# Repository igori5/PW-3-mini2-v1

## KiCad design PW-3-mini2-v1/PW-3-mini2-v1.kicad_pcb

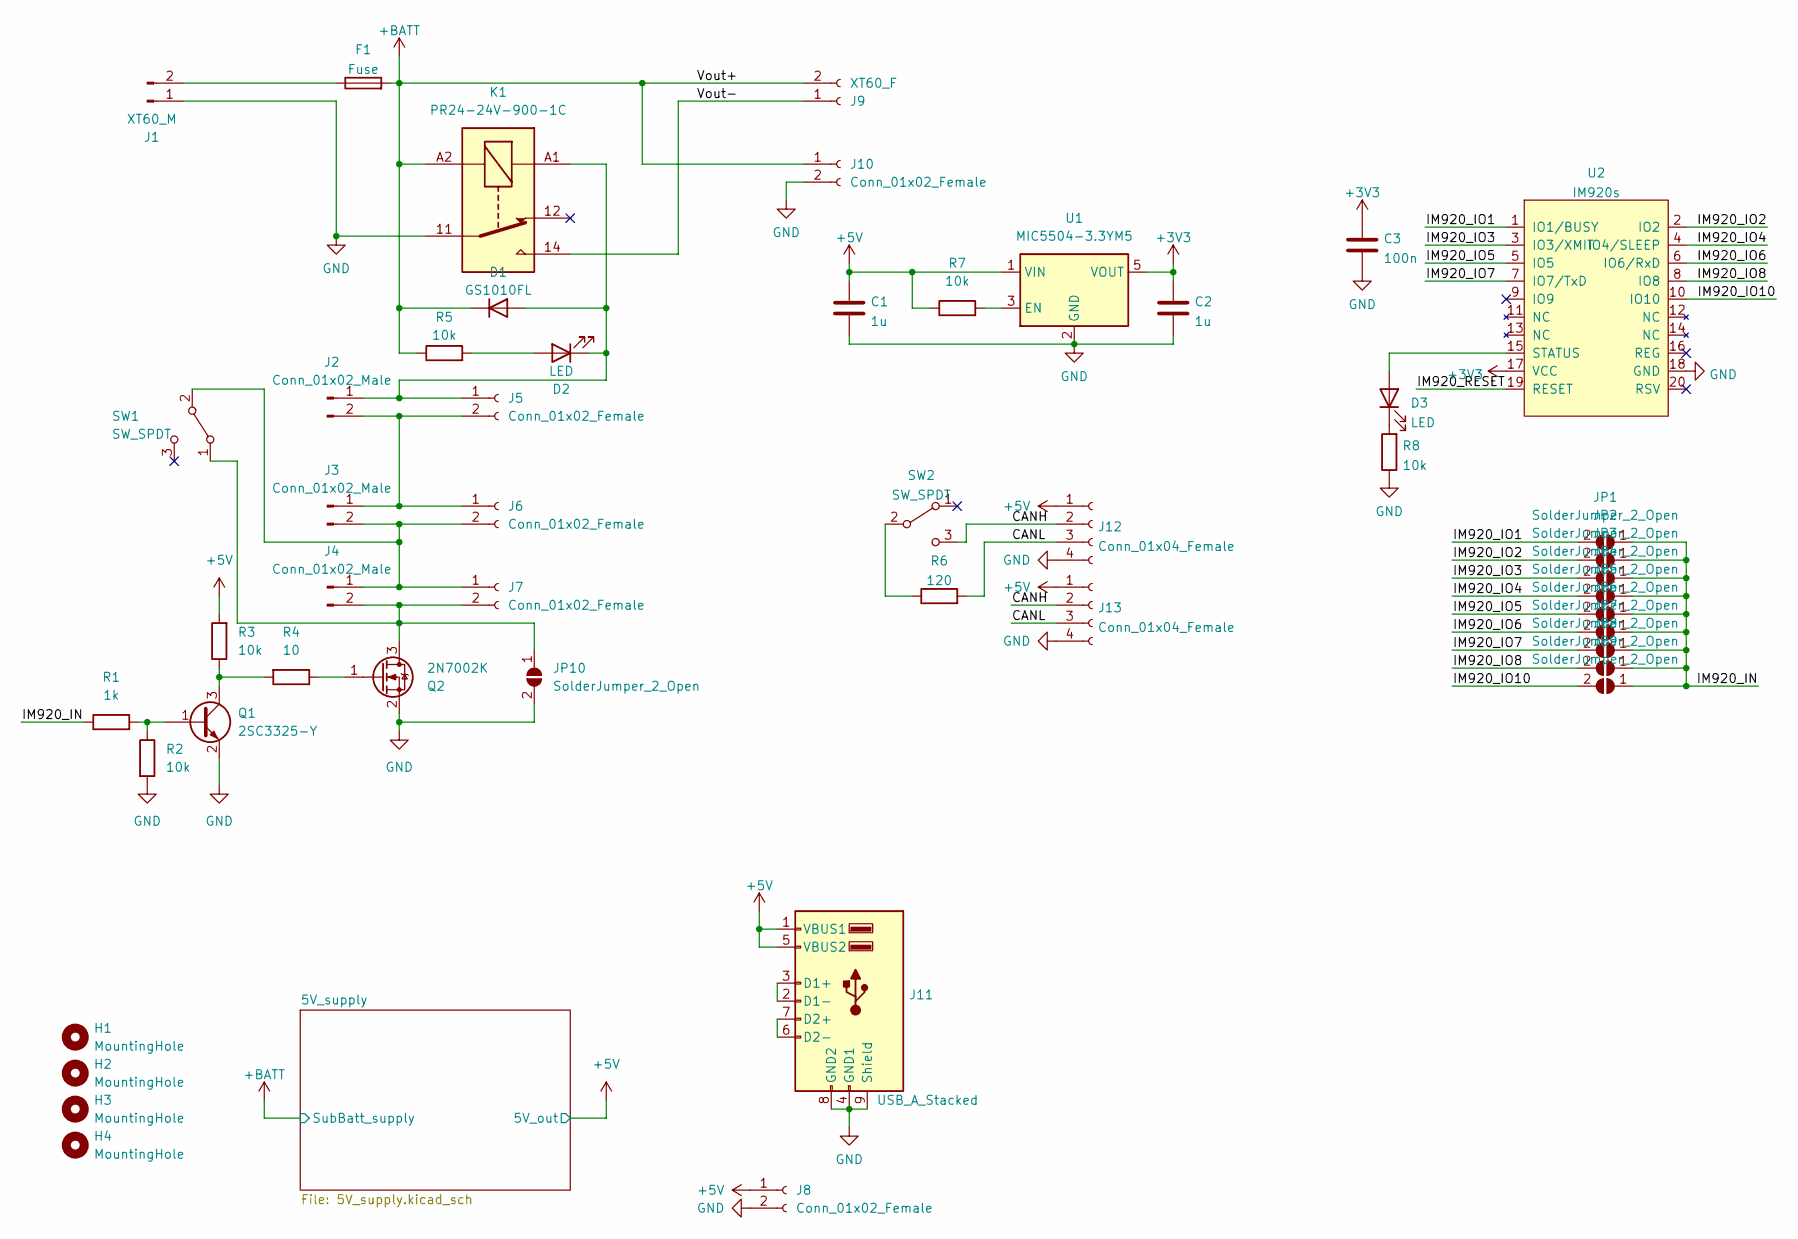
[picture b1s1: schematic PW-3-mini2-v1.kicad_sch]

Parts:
C1, C2: 1u; C_0603_1608Metric
C3: 100n; C_0603_1608Metric
D1: GS1010FL; D_SOD-123
D2, D3: LED; LED_0603_1608Metric
F1: Fuse; Fuseholder_Keystone_3568
H1, H2, H3, H4: MountingHole; MountingHole_3.2mm_M3
J1: XT60_M; AMASS_XT60PW-M_1x02_P7.20mm_Horizontal
J2, J3, J4: Conn_01x02_Male; PinHeader_1x02_P2.54mm_Vertical
J5, J6, J7, J8: Conn_01x02_Female; JST_XA_S02B-XASK-1_1x02_P2.50mm_Horizontal
J9: XT60_F; AMASS_XT60PW-F_1x02_P7.20mm_Horizontal
J10: Conn_01x02_Female; JST_XA_B02B-XASK-1_1x02_P2.50mm_Vertical
J11: USB_A_Stacked; USB_A_Wuerth_61400826021_Horizontal_Stacked
J12, J13: Conn_01x04_Female; JST_XA_S04B-XASK-1_1x04_P2.50mm_Horizontal
JP1, JP2, JP3, JP4, JP5, JP6, JP7, JP8, JP9, JP10: SolderJumper_2_Open; SolderJumper-2_P1.3mm_Open_RoundedPad1.0x1.5mm
K1: PR24-24V-900-1C; Relay_SPDT_RAYEX-L90S
Q1: 2SC3325-Y; SOT-23
Q2: 2N7002K; SOT-23
R1: 1k; R_0603_1608Metric
R2, R3, R5, R7, R8: 10k; R_0603_1608Metric
R4: 10; R_0603_1608Metric
R6: 120; R_0603_1608Metric
SW1, SW2: SW_SPDT; PinHeader_1x03_P2.54mm_Vertical
U1: MIC5504-3.3YM5; SOT-23-5
U2: IM920s

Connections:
+3V3: C2.2, C3.2, U1.5 (VOUT), U2.17 (VCC)
+5V: C1.2, J8.1, J11.1 (VBUS1), J11.5 (VBUS2), J12.1, J13.1, R3.2, R7.1, U1.1 (VIN); also elsewhere on the board
+BATT: D1.1 (K), F1.2, J9.2, J10.1, K1.A2, R5.1; also elsewhere on the board
/CANH: J12.2, J13.2, SW2.3 (C)
/CANL: J12.3, J13.3, R6.2
/IM920_IN: JP1.1 (A), JP2.1 (A), JP3.1 (A), JP4.1 (A), JP5.1 (A), JP6.1 (A), JP7.1 (A), JP8.1 (A), JP9.1 (A), R1.1
/IM920_IO1: JP1.2 (B), U2.1 (IO1/BUSY)
/IM920_IO2: JP2.2 (B), U2.2 (IO2)
/IM920_IO3: JP3.2 (B), U2.3 (IO3/XMIT)
/IM920_IO4: JP4.2 (B), U2.4 (IO4/SLEEP)
/IM920_IO5: JP5.2 (B), U2.5 (IO5)
/IM920_IO6: JP6.2 (B), U2.6 (IO6/RxD)
/IM920_IO7: JP7.2 (B), U2.7 (IO7/TxD)
/IM920_IO8: JP8.2 (B), U2.8 (IO8)
/IM920_IO10: JP9.2 (B), U2.10 (IO10)
/IM920_RESET: U2.19 (RESET)
/Vout-: J9.1, K1.14
GND: C1.1, C2.1, C3.1, J1.1, J8.2, J10.2, J11.4 (GND1), J11.8 (GND2), J11.9 (Shield), J12.4, J13.4, JP10.2 (B), K1.11, Q1.2 (E), Q2.2 (S), R2.2, R8.1, U1.2 (GND), U2.18 (GND); also elsewhere on the board
unnamed: D1.2 (A), D2.1 (K), J2.1, J5.1, K1.A1
unnamed: D2.2 (A), R5.2
unnamed: D3.2 (A), U2.15 (STATUS)
unnamed: D3.1 (K), R8.2
unnamed: F1.1, J1.2
unnamed: J2.2, J3.1, J5.2, J6.1
unnamed: J3.2, J4.1, J6.2, J7.1, SW1.2 (B)
unnamed: J4.2, J7.2, JP10.1 (A), Q2.3 (D), SW1.1 (A)
unnamed: J11.2 (D1-), J11.3 (D1+)
unnamed: J11.6 (D2-), J11.7 (D2+)
unnamed: Q1.1 (B), R1.2, R2.1
unnamed: Q1.3 (C), R3.1, R4.2
unnamed: Q2.1 (G), R4.1
unnamed: R6.1, SW2.2 (B)
unnamed: R7.2, U1.3 (EN)

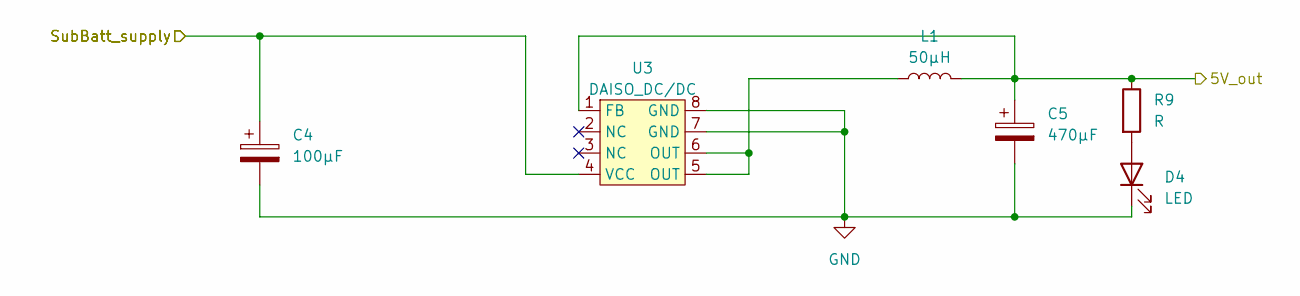
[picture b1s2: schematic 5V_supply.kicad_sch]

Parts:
C4: 100μF; CP_Radial_D6.3mm_P2.50mm
C5: 470μF; CP_Radial_D6.3mm_P2.50mm
D4: LED; LED_0603_1608Metric
L1: 50μH; L_Toroid_Vertical_L10.0mm_W5.0mm_P5.08mm
R9: R; R_0603_1608Metric
U3: DAISO_DC/DC; SOIC-8_3.9x4.9mm_P1.27mm

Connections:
+5V: C5.1, L1.2, R9.1, U3.1 (FB); also elsewhere on the board
+BATT: C4.1, U3.4 (VCC); also elsewhere on the board
GND: C4.2, C5.2, D4.1 (K), U3.7 (GND), U3.8 (GND); also elsewhere on the board
unnamed: D4.2 (A), R9.2
unnamed: L1.1, U3.5 (OUT), U3.6 (OUT)

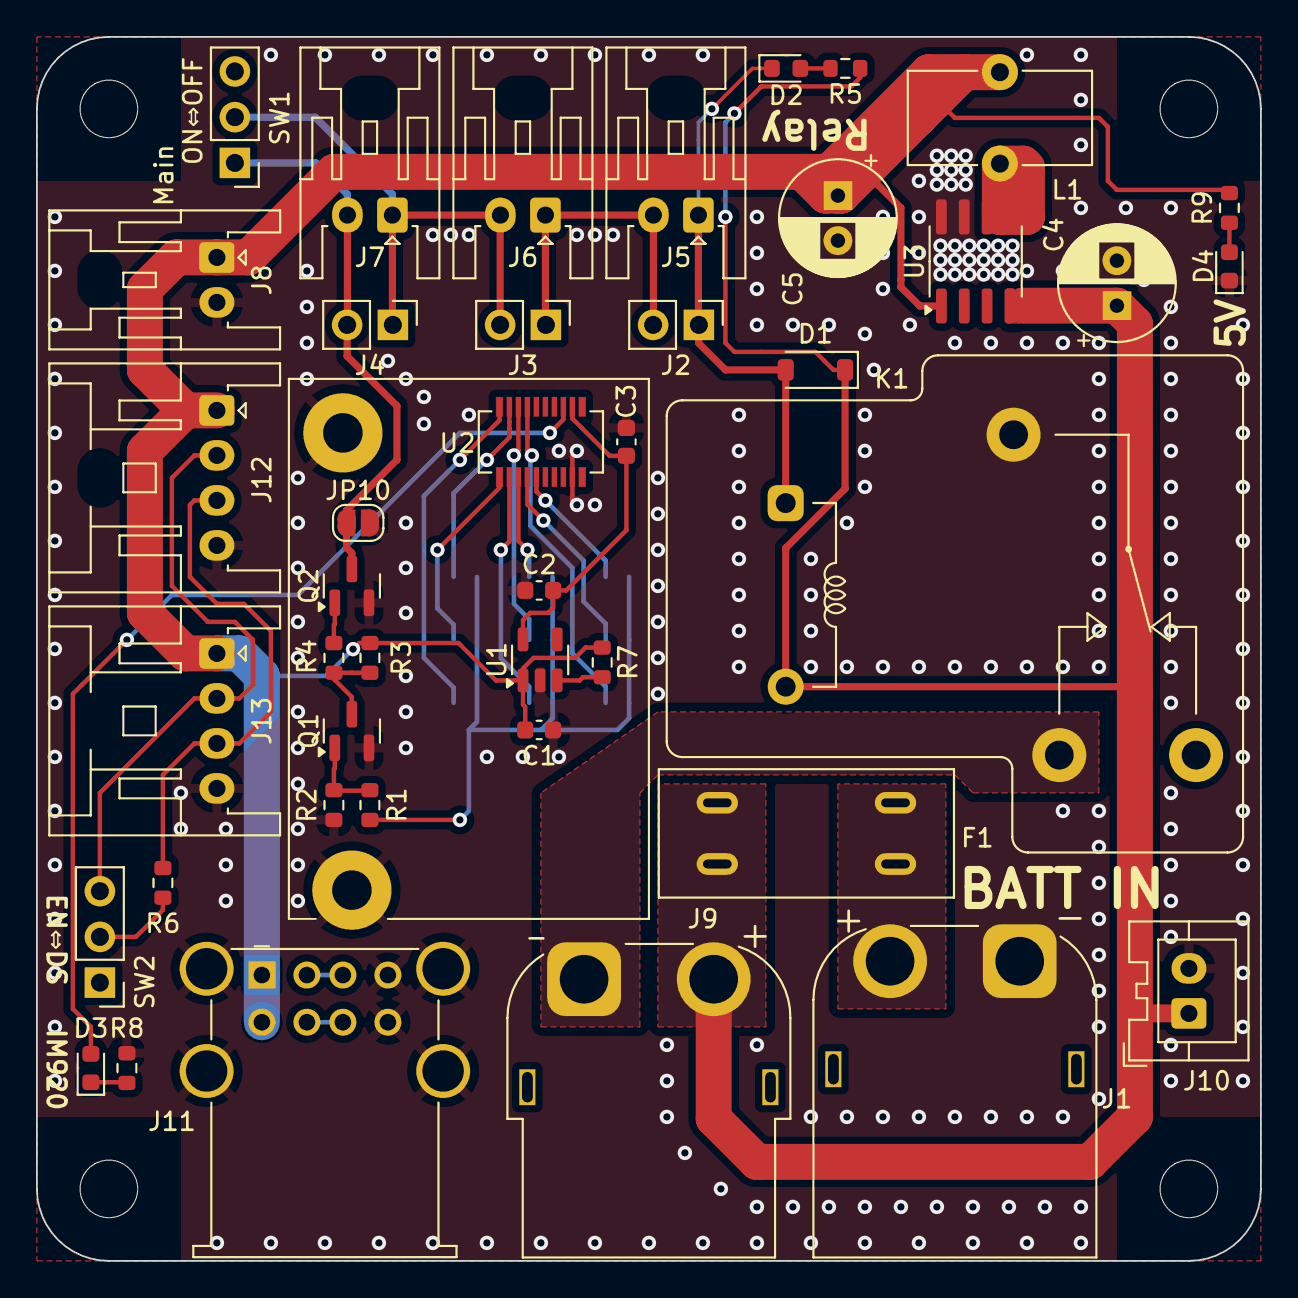
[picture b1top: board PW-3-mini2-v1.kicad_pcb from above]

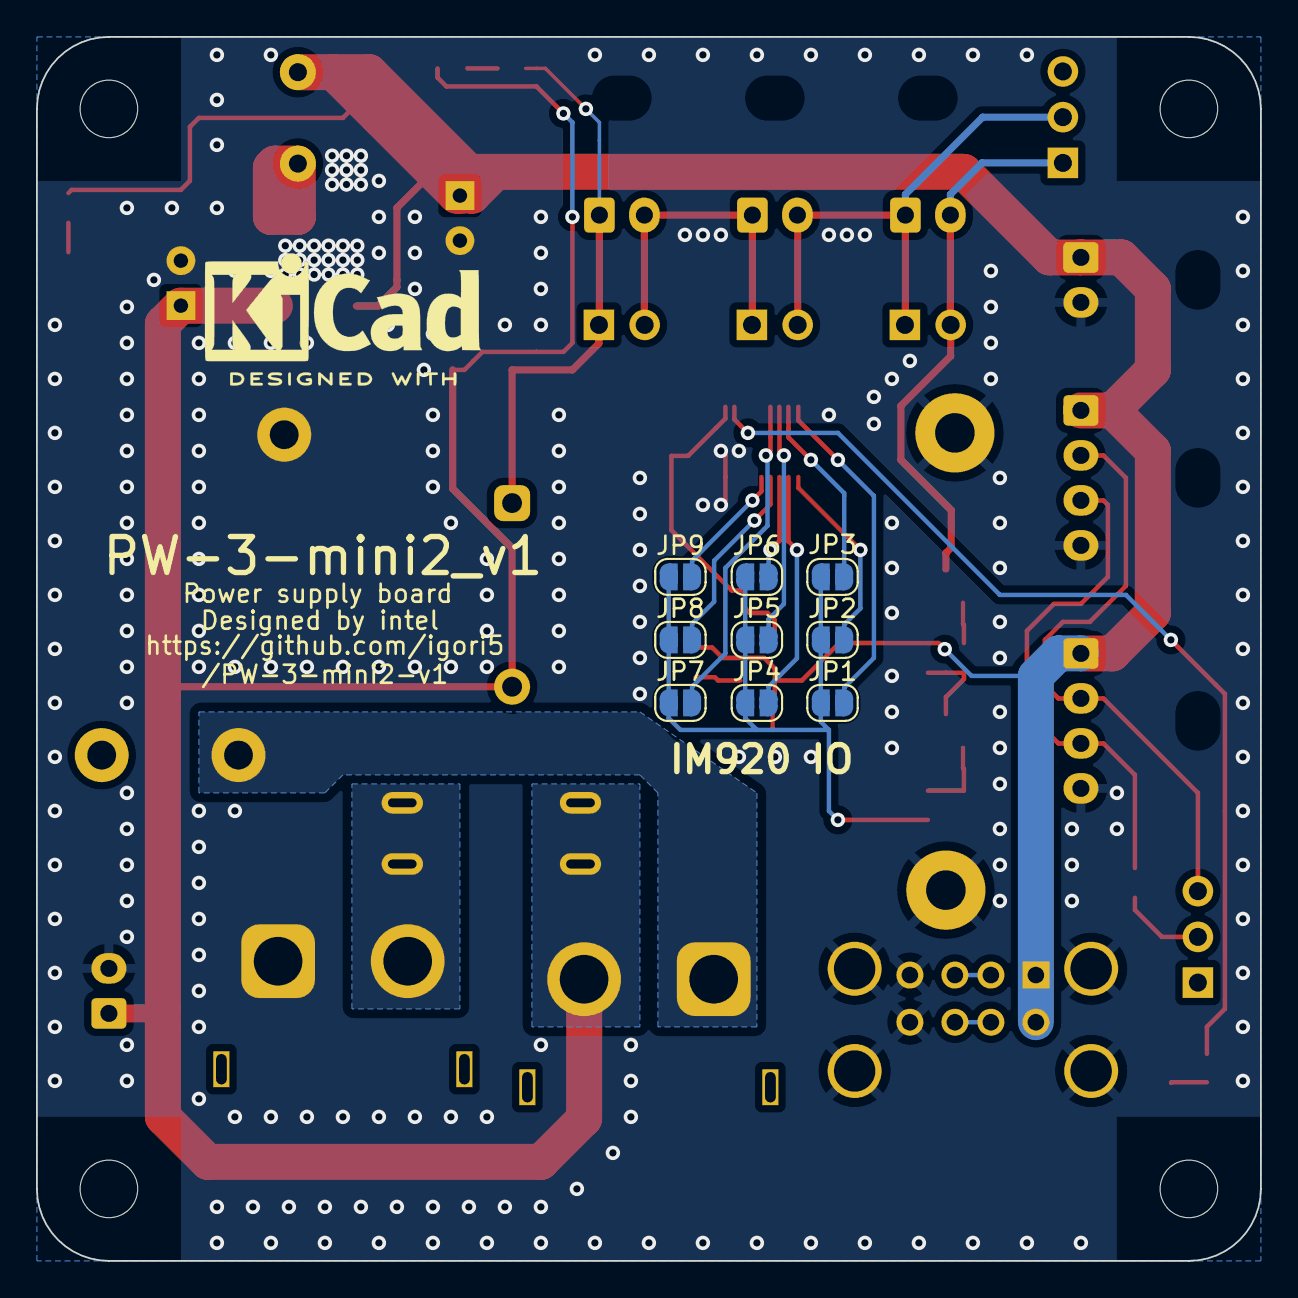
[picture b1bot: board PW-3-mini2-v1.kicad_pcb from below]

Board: 2 copper layers, 68.0 x 68.0 mm, 55 parts (9 on the bottom side), 34 nets.
